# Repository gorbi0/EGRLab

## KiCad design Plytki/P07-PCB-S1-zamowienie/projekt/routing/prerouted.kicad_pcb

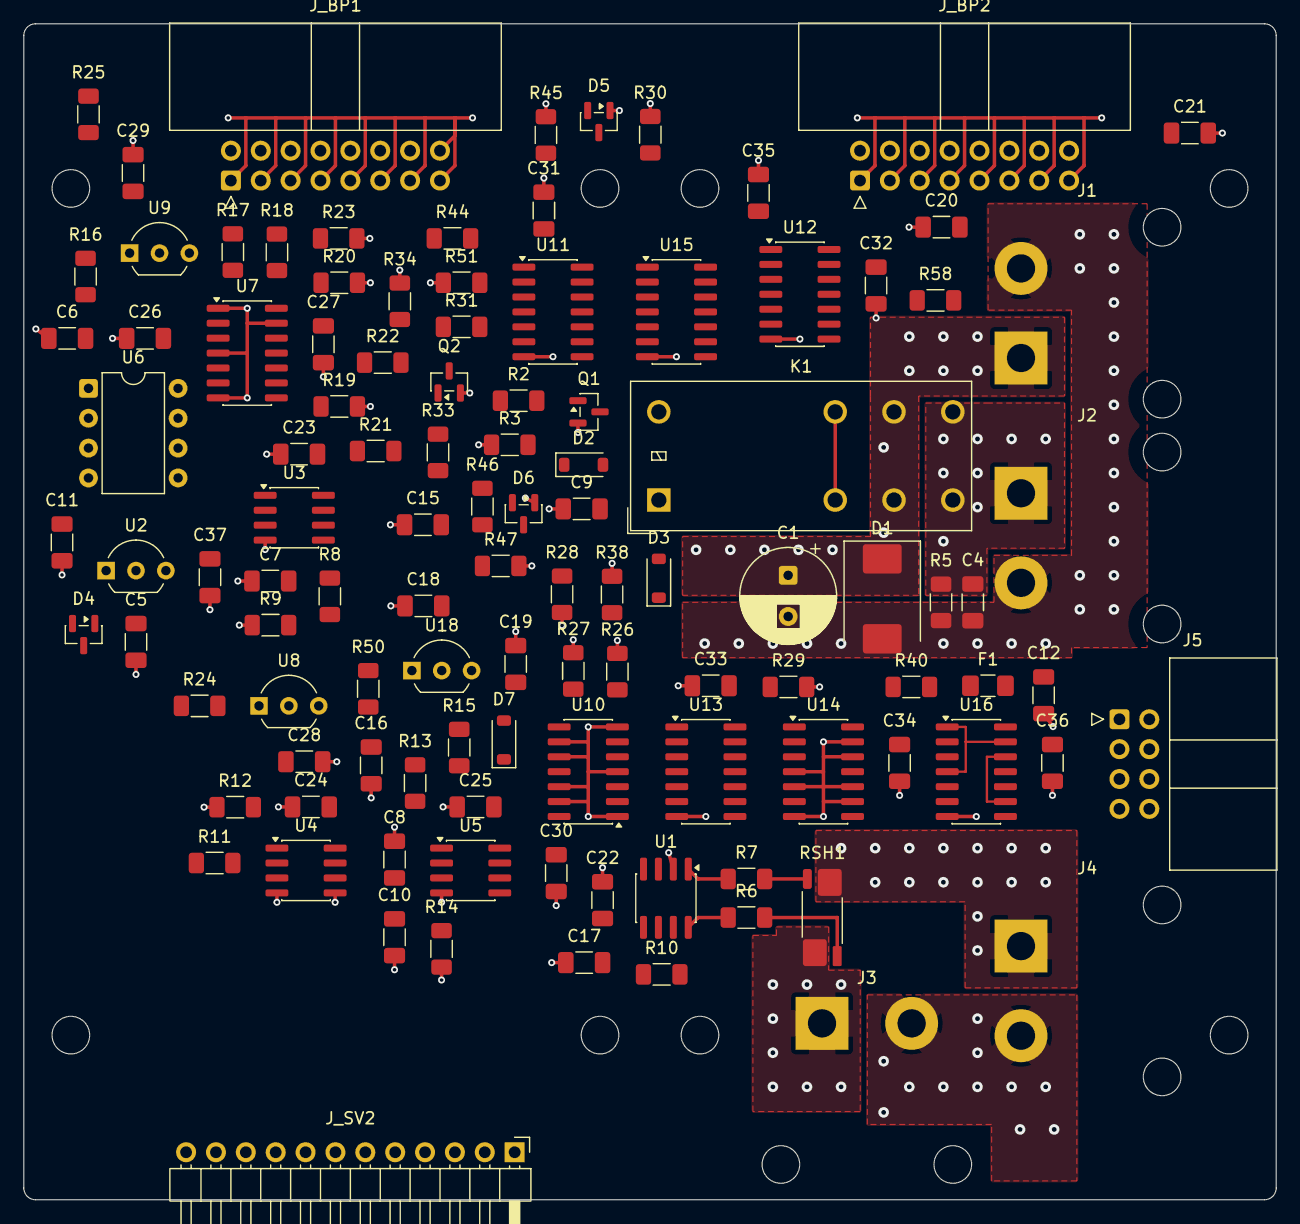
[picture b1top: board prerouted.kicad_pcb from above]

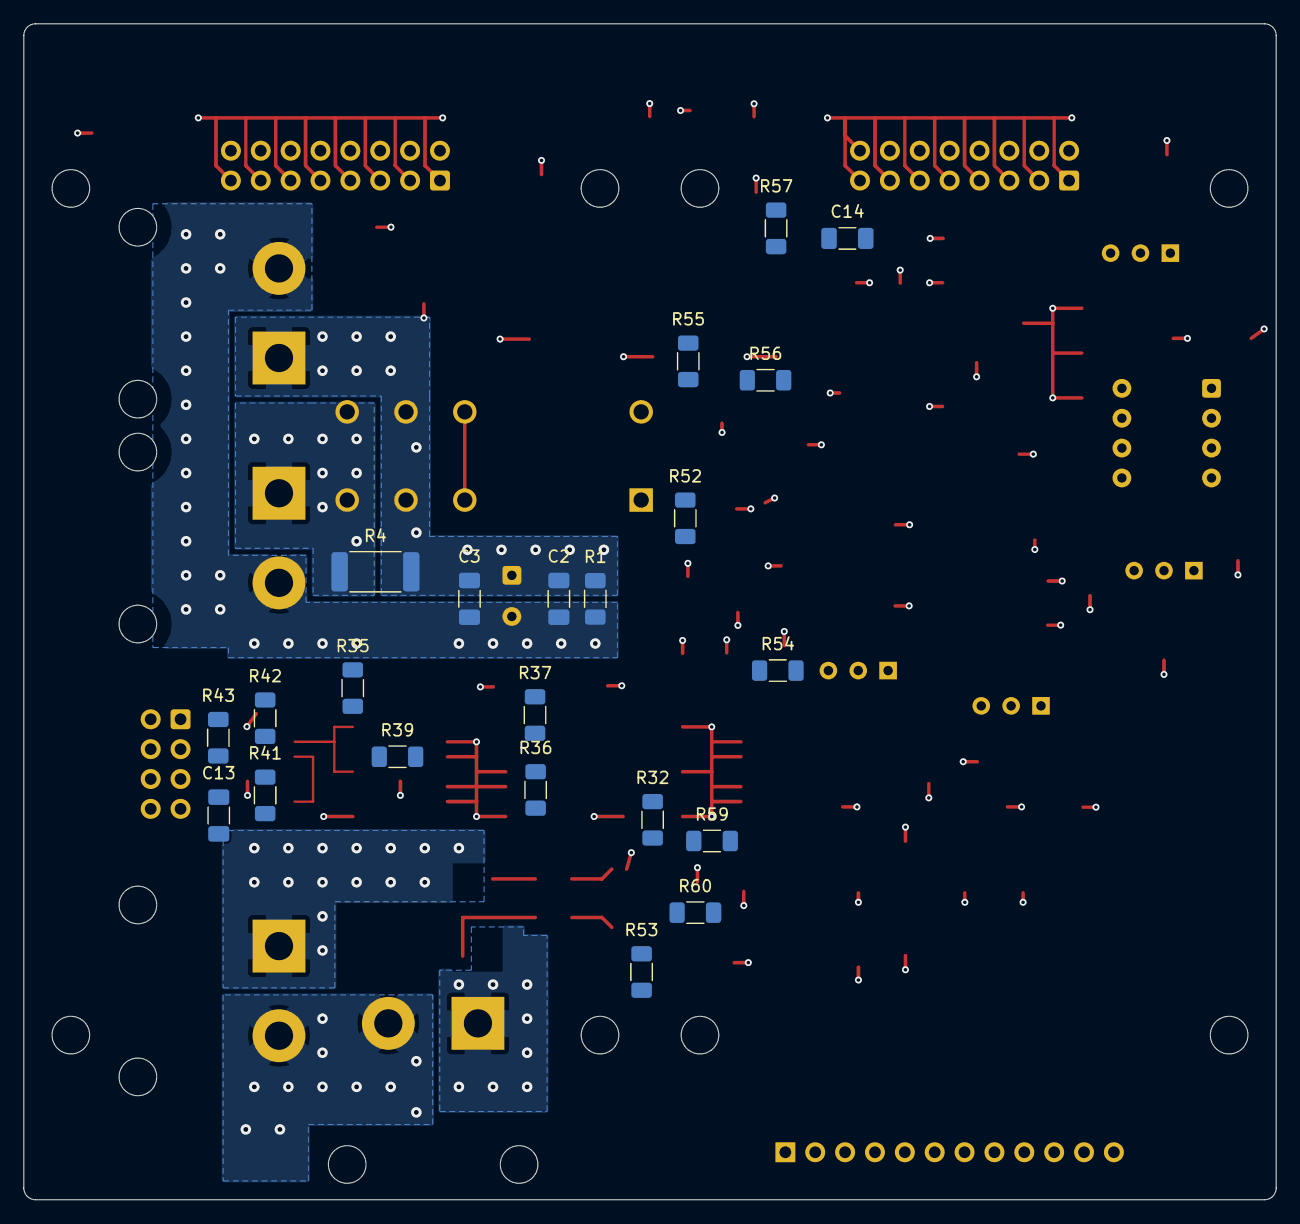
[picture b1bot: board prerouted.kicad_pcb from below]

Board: 4 copper layers, 106.5 x 100.0 mm, 140 parts (22 on the bottom side), 90 nets.

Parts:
C1: 220u; CP_Radial_D8.0mm_P3.50mm
C2, C18: 1u; C_1206_3216Metric_Pad1.33x1.80mm_HandSolder
C3, C4, C6, C7, C13, C14, C15, C17, C20, C22, C23, C24, C25, C26, C27, C28, C29, C30, C31, C32, C33, C34, C35, C36, C37: 100n; C_1206_3216Metric_Pad1.33x1.80mm_HandSolder
C5, C19: 4.7u; C_1206_3216Metric_Pad1.33x1.80mm_HandSolder
C8: 1n; C_1206_3216Metric_Pad1.33x1.80mm_HandSolder
C9, C12, C16, C21: 10u; C_1206_3216Metric_Pad1.33x1.80mm_HandSolder
C10: 10n; C_1206_3216Metric_Pad1.33x1.80mm_HandSolder
C11: 470p; C_1206_3216Metric_Pad1.33x1.80mm_HandSolder
D1: SMCJ18A; D_SMC
D2: 1N4148W; D_SOD-123
D3: BZT52C15; D_SOD-123
D4: BAT54; SOT-23
D5, D6: BAT54S; SOT-23
D7: B5819W; D_SOD-123
F1: PTC 0.12A; Fuse_1206_3216Metric_Pad1.42x1.75mm_HandSolder
H1, H2, H3, H4, H5, H6, H7, H8: M3 NPTH
J1: VMOTOR; PTH_VMOTOR
J2: MOD B+/B-; PTH_MODPWR
J3: MOD M+/M-; PTH_MODOUT
J4: TEST; PTH_TEST
J5: J_MOD; IDC-Header_2x04_P2.54mm_Horizontal
J_BP1: J_BP1; IDC-Header_2x08_P2.54mm_Horizontal
J_BP2: J_BP2; IDC-Header_2x08_P2.54mm_Horizontal
J_SV2: J_SV2 SERWIS 1x12; PinHeader_1x12_P2.54mm_Horizontal
K1: G2RL-1-E DC5; Relay_SPDT_Omron_G2RL-1-E
Q1: AO3400A; SOT-23
Q2: MMBT3904; SOT-23
R1, R5, R12, R14, R15, R18, R19, R23, R24, R25, R33, R60: 10K; R_1206_3216Metric_Pad1.30x1.75mm_HandSolder
R2, R32, R39, R40, R41, R42: 100R; R_1206_3216Metric_Pad1.30x1.75mm_HandSolder
R3, R17, R20, R26, R27, R28, R29, R30, R34, R35, R36, R37, R38, R45, R47: 100K; R_1206_3216Metric_Pad1.30x1.75mm_HandSolder
R4: 1K; R_2512_6332Metric_Pad1.40x3.35mm_HandSolder
R6, R7, R43, R50: 10R; R_1206_3216Metric_Pad1.30x1.75mm_HandSolder
R8, R9: 5.11K; R_1206_3216Metric_Pad1.30x1.75mm_HandSolder
R10, R31, R52, R53, R54, R55, R56, R57, R58, R59: 1K; R_1206_3216Metric_Pad1.30x1.75mm_HandSolder
R11: 8.06K; R_1206_3216Metric_Pad1.30x1.75mm_HandSolder
R13: 40.2K; R_1206_3216Metric_Pad1.30x1.75mm_HandSolder
R16, R22: 47R; R_1206_3216Metric_Pad1.30x1.75mm_HandSolder
R21: 47K; R_1206_3216Metric_Pad1.30x1.75mm_HandSolder
R44, R46: 4K7; R_1206_3216Metric_Pad1.30x1.75mm_HandSolder
R51: 1M; R_1206_3216Metric_Pad1.30x1.75mm_HandSolder
RSH1: 5m; R_Shunt_Vishay_WSK2512_T1.19mm_SenseE1.70
U1: INA240A2; SOIC-8_3.9x4.9mm_P1.27mm
U2: MCP1525-I/TO; TO-92_Inline_Wide
U3, U4: MCP6022-I/SN; SOIC-8_3.9x4.9mm_P1.27mm
U5: TLV1702AIDR; SOIC-8_3.9x4.9mm_P1.27mm
U6: MCP3201-BI/P; DIP-8_W7.62mm
U7, U10: 74LVC125AD; SOIC-14_3.9x8.7mm_P1.27mm
U8: MCP120-300DI/TO; TO-92_Inline_Wide
U9: MCP120-450DI/TO; TO-92_Inline_Wide
U11: 74LVC14AD; SOIC-14_3.9x8.7mm_P1.27mm
U12, U13, U14: SN74HC08D; SOIC-14_3.9x8.7mm_P1.27mm
U15: SN74HC74D; SOIC-14_3.9x8.7mm_P1.27mm
U16: 74AHCT125D; SOIC-14_3.9x8.7mm_P1.27mm
U18: MCP1702-3302E/TO; TO-92_Inline_Wide

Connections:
3V3A_P07: C19.1, C23.1, C26.1, C27.1, C28.1, C37.1, D4.3, D7.2, R17.1, R18.1, R21.1, R24.1, R54.1, U2.3, U3.8, U6.8, U7.14, U8.2, U18.3
3V3_IO: C20.1, C21.1, C30.1, C31.1, C32.1, C33.1, C34.1, C35.1, D5.2, D6.2, J_BP2.14, R15.2, U10.14, U11.13, U11.14, U12.14, U13.14, U14.14, U15.4, U15.12, U15.14
5VA_P07: C16.1, C17.1, C18.1, C22.1, C24.1, C25.1, C29.1, D7.1, R25.1, R50.2, R53.1, U1.6, U4.8, U5.8, U9.2, U18.2
5V_MOD: C12.1, C13.1, C36.1, F1.2, J5.7, R35.1, U16.14
5V_SYS: C9.1, D3.2, F1.1, J_BP2.10, J_BP2.12, K1.A1, R50.1, R52.1
/ANA/INA_MINUS: R7.2, U1.1
/ANA/INA_PLUS: R6.2, U1.8
/ANA/I_DIV: C7.1, R8.2, R9.1, U3.3
/ANA/I_FILT: C8.1, R10.2, U5.3, U5.6
/ANA/OC_FB: R11.2, R12.1, U4.2
/ANA/OC_HIGH: R11.1, U4.1, U5.5
/ANA/OC_LOW: C10.1, R13.2, R14.1, U5.2
/ANA/OC_UNUSED: U4.6, U4.7
/ANA/REF_BUF: R13.1, U1.3, U1.7, U3.6, U3.7, U4.3
/DIG/ADC_AIN: C11.1, R16.2, U6.2
/DIG/ADC_DOUT: R21.2, U6.6, U7.9
/DIG/CLK_LOCAL: R19.1, U6.7, U7.6
/DIG/CS_LOCAL_N: R18.2, U6.5, U7.3, U7.10
/DIG/DOUT_TX: R22.1, U7.8
/LOGIKA/DRIVE_OK_L: R32.1, U13.6
/LOGIKA/INA_P07: U10.3, U13.13
/LOGIKA/INB_P07: U10.6, U14.2
/LOGIKA/LOCAL_CLEAR_N: U12.6, U15.1
/LOGIKA/NO_TRIP: U13.5, U15.9
/LOGIKA/OC_B: Q2.1, R33.2, R34.1
/LOGIKA/OC_FAULT: R33.1, U11.2
/LOGIKA/PERMIT_ARMED: U12.8, U12.12
/LOGIKA/PERMIT_N: U11.4, U15.2
/LOGIKA/PWM_EN: U13.8, U13.12, U14.1
/LOGIKA/RAILS_OK: U12.3, U12.4, U12.13, U13.4, U15.10
/LOGIKA/SAFE_BAD: U11.6, U11.9
/LOGIKA/SAFE_SENSE: R31.2, R51.1, U11.5
/LOGIKA/SUP3_N: R24.2, U8.1, U12.1
/MOC/KPWR_B: Q1.1, R2.2, R3.1
/MOC/KPWR_CLAMP: D2.1, D3.1
/MOC/MOD_BP: C4.1, J2.1, K1.14, R4.2, R5.1
/MOC/MOD_MP: J3.1, RSH1.1
/MOC/T_EGR_P1: J4.1, RSH1.4
/MOC/T_EGR_P3: J3.2, J4.2
/MODUL/LEN_D: R42.1, U16.11
/MODUL/LPWM: J5.2, R40.2
/MODUL/LPWM_D: R40.1, U16.6
/MODUL/L_EN: J5.4, R42.2
/MODUL/L_IS: J5.6, R46.1
/MODUL/MOD_GND: J5.8, R43.2
/MODUL/REN_D: R41.1, U16.8
/MODUL/RPWM: J5.1, R39.2
/MODUL/RPWM_D: R39.1, U16.3
/MODUL/R_EN: J5.3, R41.2
/MODUL/R_IS: J5.5, R44.1
/SERWIS/SRV_3V3A_P07: J_SV2.4, R54.2
/SERWIS/SRV_5VA_P07: J_SV2.3, R53.2
/SERWIS/SRV_5V_SYS: J_SV2.2, R52.2
/SERWIS/SRV_DRIVE_OK: J_SV2.9, R59.2
/SERWIS/SRV_I_T_OUT: J_SV2.11, R60.2
/SERWIS/SRV_KPWR_COIL_LOW: J_SV2.5, R55.2
/SERWIS/SRV_OC_GOOD: J_SV2.8, R58.2
/SERWIS/SRV_OC_LOCAL_N: J_SV2.7, R57.2
/SERWIS/SRV_SAFE_OK: J_SV2.6, R56.2
ADC_BUF: R16.1, U3.1, U3.2
ADC_DOUTA: J_BP1.4, R22.2
ADC_SCLK: J_BP1.2, R20.1, U7.5
ARM_CLK: J_BP2.6, R30.1, U15.3, U15.11
CS_ITEST_N: J_BP1.6, R17.2, U7.2
DRIVE_EN: R38.1, U11.11, U13.3, U13.10, U16.9, U16.12
DRIVE_OK: J_BP2.8, R32.2, R59.1
DRV_OFF: R35.2, U11.10, U16.1, U16.4, U16.10, U16.13
ENA_DIAG: C14.1, D5.3, J_BP1.12, R44.2, R45.1
ENB_DIAG: C15.1, D6.3, J_BP1.14, R46.2, R47.1
GND: C5.2, C6.2, C7.2, C8.2, C9.2, C10.2, C11.2, C12.2, C13.2, C14.2, C15.2, C16.2, C17.2, C18.2, C19.2, C20.2, C21.2, C22.2, C23.2, C24.2, C25.2, C26.2, C27.2, C28.2, C29.2, C30.2, C31.2, C32.2, C33.2, C34.2, C35.2, C36.2, C37.2, D5.1, D6.1, J_BP1.1, J_BP1.3, J_BP1.5, J_BP1.7, J_BP1.9, J_BP1.11, J_BP1.13, J_BP1.15, J_BP1.16, J_BP2.1, J_BP2.3, J_BP2.5, J_BP2.7, J_BP2.9, J_BP2.11, J_BP2.13, J_BP2.15, J_SV2.1, J_SV2.10, J_SV2.12, Q1.2, Q2.2, R3.2, R9.2, R12.2, R14.2, R19.2, R20.2, R23.2, R26.2, R27.2, R28.2, R29.2, R30.2, R34.2, R36.2, R37.2, R38.2, R43.1, R45.2, R47.2, R51.2, U1.2, U2.1, U3.4, U4.4, U4.5, U5.4, U6.3, U6.4, U7.1, U7.4, U7.7, U7.13, U8.3, U9.3, U10.1, U10.4, U10.7, U10.9, U10.10, U10.12, U10.13, U11.7, U12.7, U13.7, U14.4, U14.5, U14.7, U14.9, U14.10, U14.12, U14.13, U15.7, U16.7, U18.1
I_T_OUT: R8.1, R10.1, R60.1, U1.5
KPWR_COIL_LOW: D2.2, K1.A2, Q1.3, R55.1
K_MINUS: R7.1, RSH1.3
K_PLUS: R6.1, RSH1.2
LOCAL_PERMIT: R2.1, U12.11, U13.1
LPWM_L: R37.1, U14.3, U16.5
MOTOR_INA: J_BP1.8, R26.1, U10.2
MOTOR_INB: J_BP1.10, R27.1, U10.5
MOTOR_PERMIT: J_BP2.2, R28.1, U11.3, U12.9
OC_GOOD: R58.1, U12.10, U15.5
OC_LOCAL_N: R15.1, R57.1, U5.1, U5.7, U11.1, U12.5, U15.13
PGND: C1.2, C2.2, C3.2, C4.2, D1.2, J1.2, J2.2, R1.2, R5.2
PWM_OUT: J_BP2.4, R29.1, U13.9
REF25: C5.1, C6.1, D4.1, U2.2, U3.5, U6.1
RPWM_L: R36.1, U13.11, U16.2
SAFE_N: J_BP2.16, Q2.3, R31.1
SAFE_OK: R56.1, U11.8, U13.2
SUP5_N: R23.1, U7.11, U12.2
SUP5_RAW: R25.2, U7.12, U9.1
VMOTOR: C1.1, C2.1, C3.1, D1.1, J1.1, K1.11, R1.1, R4.1

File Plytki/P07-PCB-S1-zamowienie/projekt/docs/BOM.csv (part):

ref;source_ref;display;mpn;qty;footprint;zrodlo;url;note
C1;C_BULK;220u / 35V;"EEU-FR1V221 (Panasonic FR, D8 x 11.5 mm, low ESR; MPN to confirm)";1;Capacitor_THT:CP_Radial_D8.0mm_P3.50mm;nowe;;Local bulk at the input (v6.1: 1000u/50V). Standing, 11.5 mm + 2 mm <= 16.5 mm.
C2;C_MOTOR_MF;1u;SMD 1206 X7R 50V 10% 1u;1;Capacitor_SMD:C_1206_3216Metric_Pad1.33x1.80mm_HandSolder;nowe;;
C3;C_MOTOR_HF;100n;SMD 1206 X7R 50V 10% 100n;1;Capacitor_SMD:C_1206_3216Metric_Pad1.33x1.80mm_HandSolder;nowe;;
C4;ADD_MODBP_HF;100n;SMD 1206 X7R 50V 10% 100n;1;Capacitor_SMD:C_1206_3216Metric_Pad1.33x1.80mm_HandSolder;nowe;;
C5;C_REF;4.7u;SMD 1206 X7R 25V 10% 4.7u;1;Capacitor_SMD:C_1206_3216Metric_Pad1.33x1.80mm_HandSolder;nowe;;
C6;C_REF_HF;100n;SMD 1206 X7R 50V 10% 100n;1;Capacitor_SMD:C_1206_3216Metric_Pad1.33x1.80mm_HandSolder;nowe;;At VREF of U6 (MCP3201).
C7;C_DIV;100n;"SMD 1206 C0G 50V 5% 100n (e.g. Murata GRM31C5C1H104JA01; MPN to confirm)";1;Capacitor_SMD:C_1206_3216Metric_Pad1.33x1.80mm_HandSolder;nowe;;"Disputed: anti-alias for 2 kS/s: tau = 2.555k x 100n = 0.26 ms (623 Hz). v6.1: 4.7n (4.7 us); P06 R2: 470n (133 Hz)."
C8;C_IFILT;1n;SMD 1206 C0G 50V 5% 1n;1;Capacitor_SMD:C_1206_3216Metric_Pad1.33x1.80mm_HandSolder;nowe;;
C9;ADD_KPWR_COIL_C;10u;SMD 1206 X7R 16V 10% 10u;1;Capacitor_SMD:C_1206_3216Metric_Pad1.33x1.80mm_HandSolder;nowe;;At K1.A1: local charge for the 80 mA coil step on 5V_SYS (user decision 5.10 (1)).
C10;C_OC_LOW;10n;SMD 1206 C0G 50V 5% 10n;1;Capacitor_SMD:C_1206_3216Metric_Pad1.33x1.80mm_HandSolder;nowe;;
C11;C_ADC_IN;470p;SMD 1206 C0G 50V 5% 470p;1;Capacitor_SMD:C_1206_3216Metric_Pad1.33x1.80mm_HandSolder;nowe;;
C12;ADD_5VMOD_BULK;10u;SMD 1206 X7R 16V 10% 10u;1;Capacitor_SMD:C_1206_3216Metric_Pad1.33x1.80mm_HandSolder;nowe;;
C13;ADD_5VMOD_HF;100n;SMD 1206 X7R 50V 10% 100n;1;Capacitor_SMD:C_1206_3216Metric_Pad1.33x1.80mm_HandSolder;nowe;;At J5.7 (module VCC).
C14;ADD_R_IS_C;100n;SMD 1206 X7R 50V 10% 100n;1;Capacitor_SMD:C_1206_3216Metric_Pad1.33x1.80mm_HandSolder;nowe;;tau = (14.7k || 9.1k) x 100n = 0.56 ms: averages PWM.
C15;ADD_L_IS_C;100n;SMD 1206 X7R 50V 10% 100n;1;Capacitor_SMD:C_1206_3216Metric_Pad1.33x1.80mm_HandSolder;nowe;;tau = (14.7k || 9.1k) x 100n = 0.56 ms: averages PWM.
C16;C_AF;10u;SMD 1206 X7R 16V 10% 10u;1;Capacitor_SMD:C_1206_3216Metric_Pad1.33x1.80mm_HandSolder;nowe;;
C17;ADD_5VA_HF;100n;SMD 1206 X7R 50V 10% 100n;1;Capacitor_SMD:C_1206_3216Metric_Pad1.33x1.80mm_HandSolder;nowe;;
C18;C_LDO_IN;1u;SMD 1206 X7R 50V 10% 1u;1;Capacitor_SMD:C_1206_3216Metric_Pad1.33x1.80mm_HandSolder;nowe;;
C19;C_LDO_OUT;4.7u;SMD 1206 X7R 25V 10% 4.7u;1;Capacitor_SMD:C_1206_3216Metric_Pad1.33x1.80mm_HandSolder;nowe;;
C20;ADD_3V3IO_HF;100n;SMD 1206 X7R 50V 10% 100n;1;Capacitor_SMD:C_1206_3216Metric_Pad1.33x1.80mm_HandSolder;nowe;;
C21;ADD_3V3IO_BULK;10u;SMD 1206 X7R 16V 10% 10u;1;Capacitor_SMD:C_1206_3216Metric_Pad1.33x1.80mm_HandSolder;nowe;;
C22;DEC_U1;100n;SMD 1206 X7R 50V 10% 100n;1;Capacitor_SMD:C_1206_3216Metric_Pad1.33x1.80mm_HandSolder;nowe;;Decoupling at U1.
C23;DEC_U3;100n;SMD 1206 X7R 50V 10% 100n;1;Capacitor_SMD:C_1206_3216Metric_Pad1.33x1.80mm_HandSolder;nowe;;Decoupling at U3.
C24;DEC_U4;100n;SMD 1206 X7R 50V 10% 100n;1;Capacitor_SMD:C_1206_3216Metric_Pad1.33x1.80mm_HandSolder;nowe;;Decoupling at U4.
C25;DEC_U5;100n;SMD 1206 X7R 50V 10% 100n;1;Capacitor_SMD:C_1206_3216Metric_Pad1.33x1.80mm_HandSolder;nowe;;Decoupling at U5.
C26;DEC_U6;100n;SMD 1206 X7R 50V 10% 100n;1;Capacitor_SMD:C_1206_3216Metric_Pad1.33x1.80mm_HandSolder;nowe;;Decoupling at U6.
C27;DEC_U7;100n;SMD 1206 X7R 50V 10% 100n;1;Capacitor_SMD:C_1206_3216Metric_Pad1.33x1.80mm_HandSolder;nowe;;Decoupling at U7.
C28;DEC_U8;100n;SMD 1206 X7R 50V 10% 100n;1;Capacitor_SMD:C_1206_3216Metric_Pad1.33x1.80mm_HandSolder;nowe;;Decoupling at U8.
C29;DEC_U9;100n;SMD 1206 X7R 50V 10% 100n;1;Capacitor_SMD:C_1206_3216Metric_Pad1.33x1.80mm_HandSolder;nowe;;Decoupling at U9.
C30;DEC_U10;100n;SMD 1206 X7R 50V 10% 100n;1;Capacitor_SMD:C_1206_3216Metric_Pad1.33x1.80mm_HandSolder;nowe;;Decoupling at U10.
C31;DEC_U11;100n;SMD 1206 X7R 50V 10% 100n;1;Capacitor_SMD:C_1206_3216Metric_Pad1.33x1.80mm_HandSolder;nowe;;Decoupling at U11.
C32;DEC_U12;100n;SMD 1206 X7R 50V 10% 100n;1;Capacitor_SMD:C_1206_3216Metric_Pad1.33x1.80mm_HandSolder;nowe;;Decoupling at U12.
C33;DEC_U13;100n;SMD 1206 X7R 50V 10% 100n;1;Capacitor_SMD:C_1206_3216Metric_Pad1.33x1.80mm_HandSolder;nowe;;Decoupling at U13.
C34;DEC_U14;100n;SMD 1206 X7R 50V 10% 100n;1;Capacitor_SMD:C_1206_3216Metric_Pad1.33x1.80mm_HandSolder;nowe;;Decoupling at U14.
C35;DEC_U15;100n;SMD 1206 X7R 50V 10% 100n;1;Capacitor_SMD:C_1206_3216Metric_Pad1.33x1.80mm_HandSolder;nowe;;Decoupling at U15.
C36;DEC_U16;100n;SMD 1206 X7R 50V 10% 100n;1;Capacitor_SMD:C_1206_3216Metric_Pad1.33x1.80mm_HandSolder;nowe;;Decoupling at U16.
C37;DEC_U2;100n;SMD 1206 X7R 50V 10% 100n;1;Capacitor_SMD:C_1206_3216Metric_Pad1.33x1.80mm_HandSolder;nowe;;Decoupling at U2.
D1;D2;SMCJ18A;SMCJ18A (Littelfuse, 1.5 kW, VRWM 18 V);1;Diode_SMD:D_SMC;nowe;;TVS at VMOTOR as v6.1 D2: VRWM 18 V >= 16.8 V (4S full), VC ~29 V << 40 V BTS7960 and relay contacts.
D2;D11;1N4148W;1N4148W (SOD-123, 100 V);1;Diode_SMD:D_SOD-123;nowe;;Coil clamp diode (anode at coil low end) in series with Zener D3 to 5V_SYS: fast release (v6.1 D11/D12).
D3;D12;BZT52C15;BZT52C15 (Zener 15 V 0.5 W, SOD-123);1;Diode_SMD:D_SOD-123;nowe;;Clamp = 5V_SYS + 15 V + 0.7 V <= 20.8 V < 85 % of 30 V VDS of Q1 (v6.1: 18 V Zener with 60 V transistor array).
D4;ADD_REF_DISCHARGE;BAT54;BAT54 (SOT-23, single);1;Package_TO_SOT_SMD:SOT-23;nowe;;Discharge of C5 into 3V3A on power removal (P06 R2 D2).
D5;ADD_R_IS_CLAMP;BAT54S;BAT54S (SOT-23, series pair);1;Package_TO_SOT_SMD:SOT-23;nowe;;"Clamp of the divided IS to GND-0.3 / 3V3_IO+0.3 V (IS up to VS = 16.8 V); protects the P03 input."
D6;ADD_L_IS_CLAMP;BAT54S;BAT54S (SOT-23, series pair);1;Package_TO_SOT_SMD:SOT-23;nowe;;"Clamp of the divided IS to GND-0.3 / 3V3_IO+0.3 V (IS up to VS = 16.8 V); protects the P03 input."
D7;ADD_LDO_DISCHARGE;B5819W;B5819W (Schottky 1 A 40 V, SOD-123);1;Diode_SMD:D_SOD-123;nowe;;Anode 3V3A, cathode 5VA: output capacitor discharge on supply removal (P06 R2 D1).
F1;ADD_MOD_VCC_PTC;PTC 0.12A;"MF-NSMF012-2 (Bourns 1206, Ihold 0.12 A, Itrip 0.29 A; MPN to confirm)";1;Fuse:Fuse_1206_3216Metric_Pad1.42x1.75mm_HandSolder;nowe;;Module VCC (74HC244 on the module) and U16: a shorted harness does not pull 5V_SYS down.
J1;J_VMOTORB;VMOTOR / PTH;2 x 2.0 mm2 from P02 R4 J2 (GMSTB plug);1;P07:PTH_VMOTOR;nowe;;"PTH solder joints + tie anchor 12 mm; 2.0 mm2 (decision 4.10). P02 R4 J2.1 VMOTOR (behind F1, MINI 7.5 A insert - user decision 5.10 (7)), J2.2 GND. See docs/WIAZKA-MODUL.md."
J2;ADD_MOD_PWR;MOD B+/B- / PTH;2 x 2.0 mm2 to module B+ / B-;1;P07:PTH_MODPWR;nowe;;To the IBT-2 screw terminals B+ / B-. PTH + anchor.
J3;ADD_MOD_OUT;MOD M+/M- / PTH;2 x 2.0 mm2 from module M+ / M-;1;P07:PTH_MODOUT;nowe;;From the IBT-2 terminals M+ / M-. M- passes through to J4.2.
J4;J_TMOTORA;TEST / PTH;2 x 2.0 mm2 to P11 port TEST (valve pins 1 / 3);1;P07:PTH_TEST;nowe;;At the x = 0 edge (task). Port TEST on the panel (P11-4: motor current by wires straight to the port).
J5;ADD_J_MOD;J_MOD / IDC 2x4;IDC box header 2x4 2.54 mm angled shrouded, Au;1;Connector_IDC:IDC-Header_2x04_P2.54mm_Horizontal;nowe;;"User decision 5.10 (3): numbering 1:1 as the module header (odd row 1 RPWM / 3 R_EN / 5 R_IS / 7 VCC, even row 2 LPWM / 4 L_EN / 6 L_IS / 8 GND). Angled box header at the board edge; 8-wire ribbon with IDC 2x4 sockets on both ends - docs/WIAZKA-MODUL.md."
J_BP1;J_ITESTB+J_DIRB;J_BP1 / IDC 2x8;IDC header 2x8 2.54mm angled shrouded, Au;1;Connector_IDC:IDC-Header_2x08_P2.54mm_Horizontal;nowe;;Edge A, slot S2 (board x = 26.5 mm, stack x = 80.0 mm), pin 1 towards smaller x. Odd pins GND, 16 GND reserve. Partner: P03 R6 (J_BP1 / J_BP2) through P12.
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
